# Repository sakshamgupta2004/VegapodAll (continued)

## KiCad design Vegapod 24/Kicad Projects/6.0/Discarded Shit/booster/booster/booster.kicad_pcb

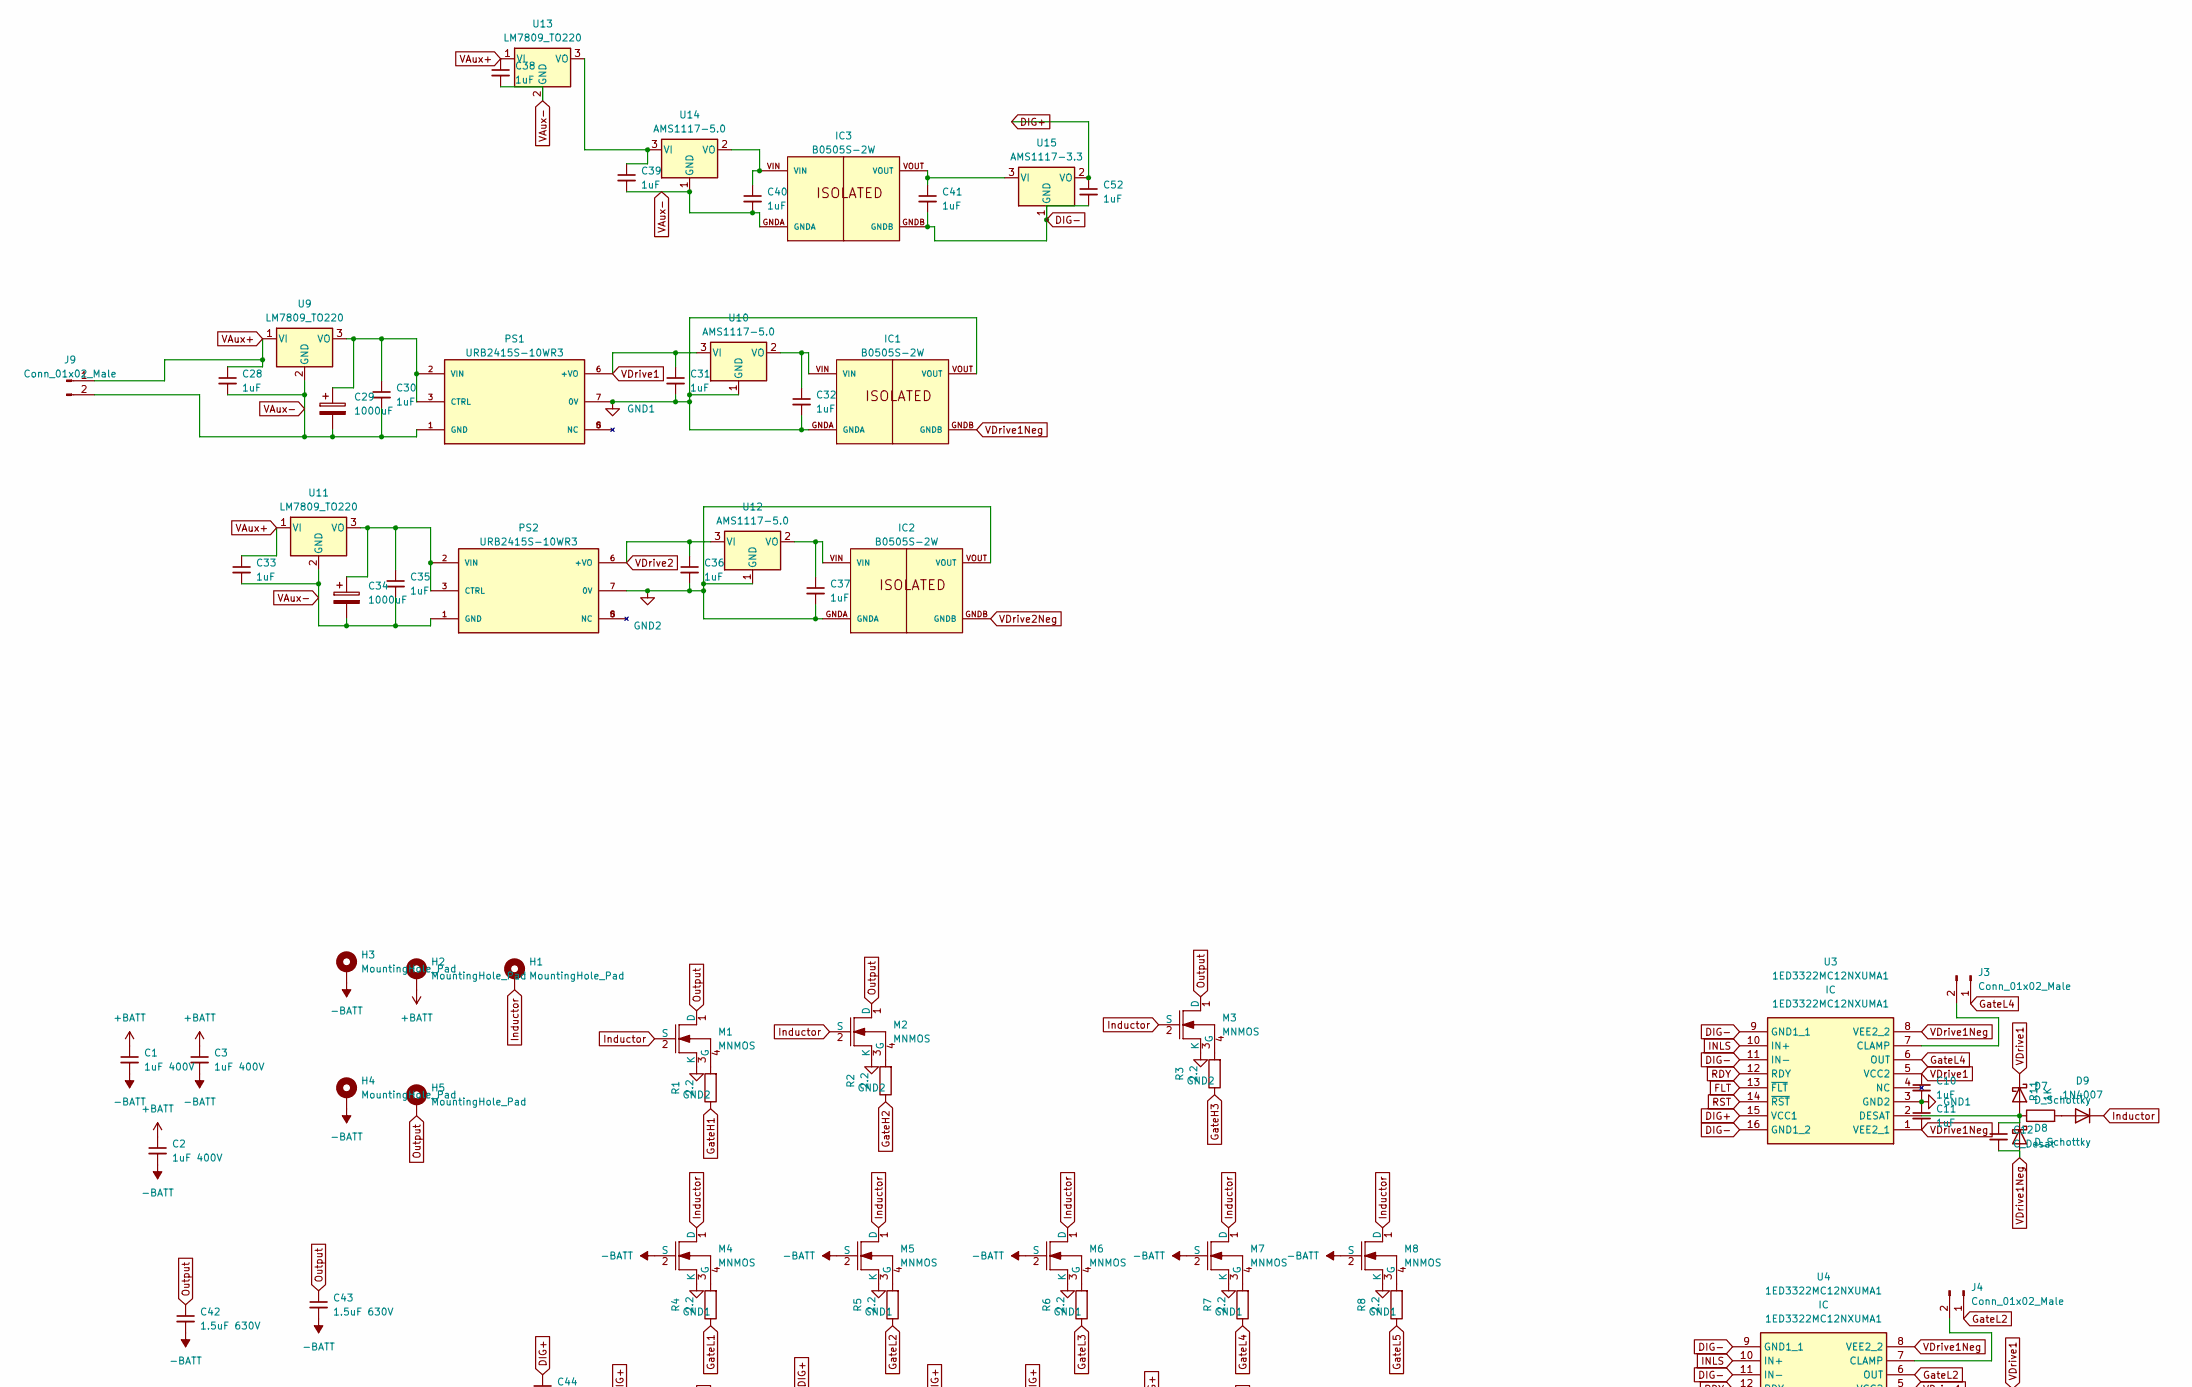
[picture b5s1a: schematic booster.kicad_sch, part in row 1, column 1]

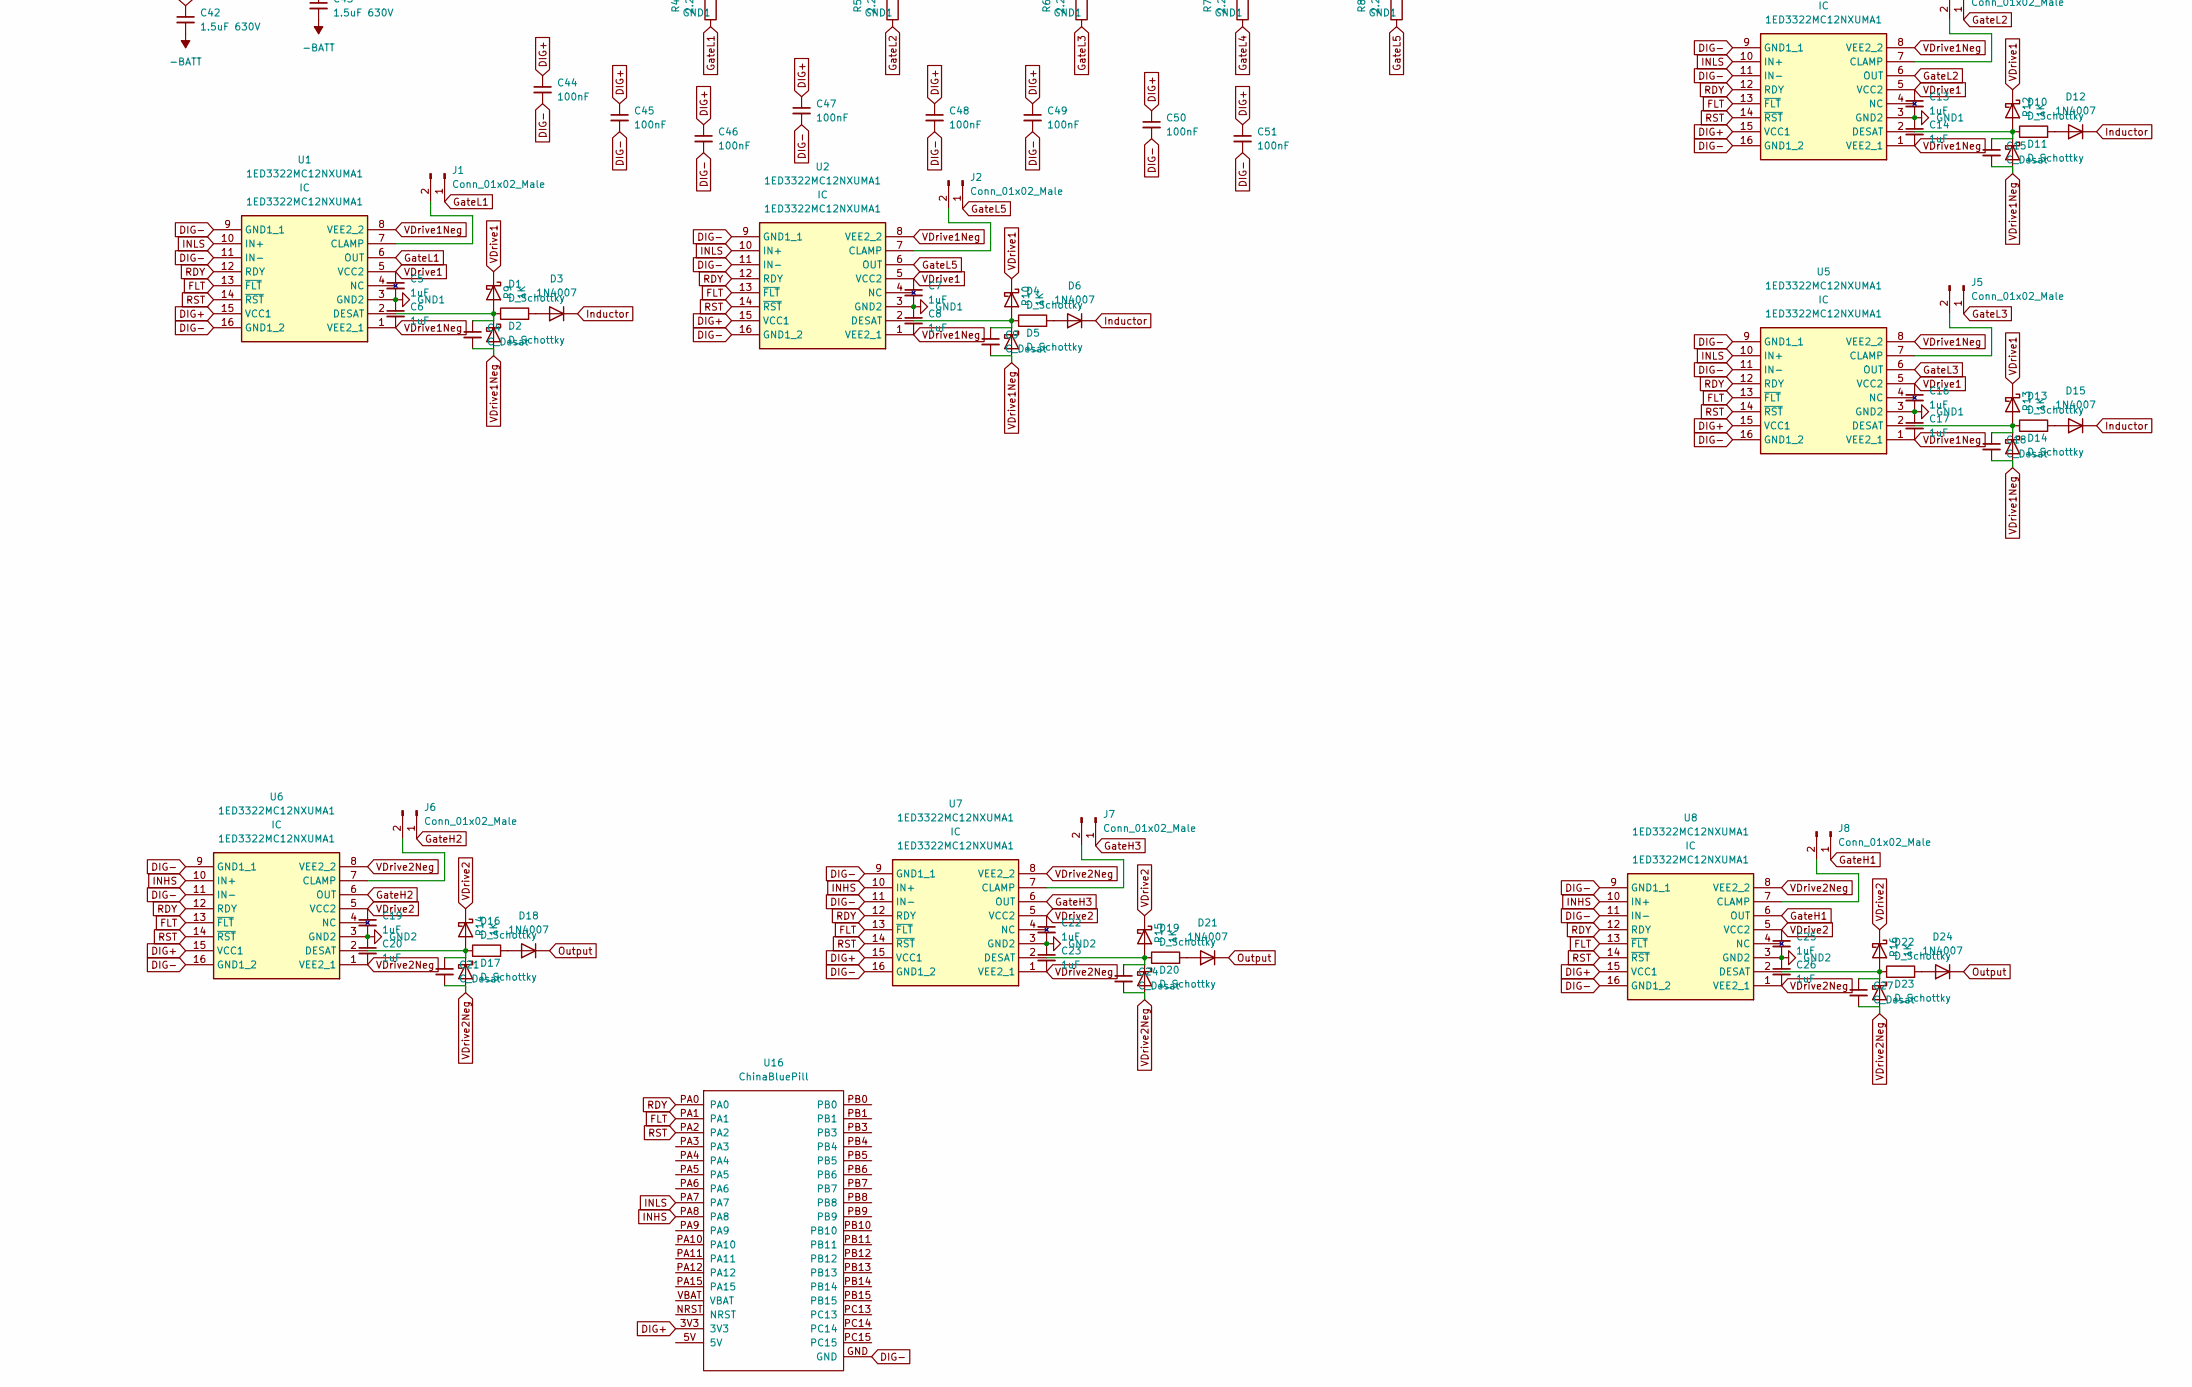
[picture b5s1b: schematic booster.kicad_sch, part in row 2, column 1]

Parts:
C1, C2, C3: 1uF 400V; C_Rect_L24.0mm_W8.3mm_P22.50mm_MKT
C4, C9, C12, C15, C18, C21, C24, C27: C_Desat; C_0603_1608Metric_Pad1.08x0.95mm_HandSolder
C5, C6, C7, C8, C10, C11, C13, C14, C16, C17, C19, C20, C22, C23, C25, C26, C28, C30, C31, C32, C33, C35, C36, C37, C38, C39, C40, C41, C52: 1uF; C_1206_3216Metric_Pad1.33x1.80mm_HandSolder
C29, C34: 1000uF; CAP_EEEFK1E102AQ
C42, C43: 1.5uF 630V; C_Rect_L29.0mm_W16.0mm_P27.50mm_MKT
C44, C45, C46, C47, C48, C49, C50, C51: 100nF; C_0603_1608Metric_Pad1.08x0.95mm_HandSolder
D1, D2, D4, D5, D7, D8, D10, D11, D13, D14, D16, D17, D19, D20, D22, D23: D_Schottky; D_SMA_Handsoldering
D3, D6, D9, D12, D15, D18, D21, D24: 1N4007; D_SMA_Handsoldering
H1, H2, H3, H4, H5: MountingHole_Pad; MountingHole_6.4mm_M6_Pad
IC1, IC2, IC3: B0505S-2W; MPN B0505S-2W; DigiKey_Part_Number 2725-B0505S-2W-ND
J1, J2, J3, J4, J5, J6, J7, J8: Conn_01x02_Male; PinHeader_1x02_P1.27mm_Vertical
J9: Conn_01x02_Male; JST_XH_S2B-XH-A_1x02_P2.50mm_Horizontal
M1, M2, M3, M4, M5, M6, M7, M8: MNMOS; TO-247-4_Horizontal_TabDown
PS1, PS2: URB2415S-10WR3; CONV_URB2415S-10WR3; PARTREV 2020.11.09-A/4; DigiKey_Part_Number 2725-URB2415S-10WR3-ND
R1, R2, R3, R4, R5, R6, R7, R8: 2.2; R_1206_3216Metric
R9, R10, R11, R12, R13, R14, R15, R16: 1K; R_0603_1608Metric_Pad0.98x0.95mm_HandSolder
U1, U2, U3, U4, U5, U6, U7, U8: 1ED3322MC12NXUMA1; SOIC127P1030X265-16N; Mouser Part Number 726-1ED3322MC12NXUMA
U9, U11, U13: LM7809_TO220; TO-220-3_Vertical
U10, U12, U14: AMS1117-5.0; SOT-223-3_TabPin2
U15: AMS1117-3.3; SOT-223-3_TabPin2
U16: ChinaBluePill

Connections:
+BATT: C1.1, C2.1, C3.1, H2.1
-BATT: C1.2, C2.2, C3.2, C42.2, C43.2, H3.1, H4.1, M4.2 (S), M5.2 (S), M6.2 (S), M7.2 (S), M8.2 (S)
DIG+: C44.1, C45.1, C46.1, C47.1, C48.1, C49.1, C50.1, C51.1, C52.1, U1.15 (VCC1), U2.15 (VCC1), U3.15 (VCC1), U4.15 (VCC1), U5.15 (VCC1), U6.15 (VCC1), U7.15 (VCC1), U8.15 (VCC1), U15.2 (VO), U16.3V3
DIG-: C41.2, C44.2, C45.2, C46.2, C47.2, C48.2, C49.2, C50.2, C51.2, C52.2, IC3.GNDB, U1.9 (GND1_1), U1.11 (IN-), U1.16 (GND1_2), U2.9 (GND1_1), U2.11 (IN-), U2.16 (GND1_2), U3.9 (GND1_1), U3.11 (IN-), U3.16 (GND1_2), U4.9 (GND1_1), U4.11 (IN-), U4.16 (GND1_2), U5.9 (GND1_1), U5.11 (IN-), U5.16 (GND1_2), U6.9 (GND1_1), U6.11 (IN-), U6.16 (GND1_2), U7.9 (GND1_1), U7.11 (IN-), U7.16 (GND1_2), U8.9 (GND1_1), U8.11 (IN-), U8.16 (GND1_2), U15.1 (GND), U16.GND
FLT: U1.13 (~FLT), U2.13 (~FLT), U3.13 (~FLT), U4.13 (~FLT), U5.13 (~FLT), U6.13 (~FLT), U7.13 (~FLT), U8.13 (~FLT), U16.PA1
GND1: C5.2, C6.1, C7.2, C8.1, C10.2, C11.1, C13.2, C14.1, C16.2, C17.1, C31.2, C32.2, IC1.GNDA, IC1.VOUT, M4.3 (K), M5.3 (K), M6.3 (K), M7.3 (K), M8.3 (K), PS1.7 (0V), U1.3 (GND2), U2.3 (GND2), U3.3 (GND2), U4.3 (GND2), U5.3 (GND2), U10.1 (GND)
GND2: C19.2, C20.1, C22.2, C23.1, C25.2, C26.1, C36.2, C37.2, IC2.GNDA, IC2.VOUT, M1.3 (K), M2.3 (K), M3.3 (K), PS2.7 (0V), U6.3 (GND2), U7.3 (GND2), U8.3 (GND2), U12.1 (GND)
GateH1: J8.1, R1.1, U8.6 (OUT)
GateH2: J6.1, R2.1, U6.6 (OUT)
GateH3: J7.1, R3.1, U7.6 (OUT)
GateL1: J1.1, R4.1, U1.6 (OUT)
GateL2: J4.1, R5.1, U4.6 (OUT)
GateL3: J5.1, R6.1, U5.6 (OUT)
GateL4: J3.1, R7.1, U3.6 (OUT)
GateL5: J2.1, R8.1, U2.6 (OUT)
INHS: U6.10 (IN+), U7.10 (IN+), U8.10 (IN+), U16.PA8
INLS: U1.10 (IN+), U2.10 (IN+), U3.10 (IN+), U4.10 (IN+), U5.10 (IN+), U16.PA7
Inductor: D3.1 (K), D6.1 (K), D9.1 (K), D12.1 (K), D15.1 (K), H1.1, M1.2 (S), M2.2 (S), M3.2 (S), M4.1 (D), M5.1 (D), M6.1 (D), M7.1 (D), M8.1 (D)
unnamed: C4.1, D1.2 (A), D2.1 (K), R9.1, U1.2 (DESAT)
unnamed: C9.1, D4.2 (A), D5.1 (K), R10.1, U2.2 (DESAT)
unnamed: C12.1, D7.2 (A), D8.1 (K), R11.1, U3.2 (DESAT)
unnamed: C15.1, D10.2 (A), D11.1 (K), R12.1, U4.2 (DESAT)
unnamed: C18.1, D13.2 (A), D14.1 (K), R13.1, U5.2 (DESAT)
unnamed: C21.1, D16.2 (A), D17.1 (K), R14.1, U6.2 (DESAT)
unnamed: C24.1, D19.2 (A), D20.1 (K), R15.1, U7.2 (DESAT)
unnamed: C27.1, D22.2 (A), D23.1 (K), R16.1, U8.2 (DESAT)
unnamed: C29.1, C30.1, PS1.2 (VIN), PS1.3 (CTRL), U9.3 (VO)
unnamed: C32.1, IC1.VIN, U10.2 (VO)
unnamed: C34.1, C35.1, PS2.2 (VIN), PS2.3 (CTRL), U11.3 (VO)
unnamed: C37.1, IC2.VIN, U12.2 (VO)
unnamed: C39.1, U13.3 (VO), U14.3 (VI)
unnamed: C40.1, IC3.VIN, U14.2 (VO)
unnamed: C41.1, IC3.VOUT, U15.3 (VI)
unnamed: D3.2 (A), R9.2
unnamed: D6.2 (A), R10.2
unnamed: D9.2 (A), R11.2
unnamed: D12.2 (A), R12.2
unnamed: D15.2 (A), R13.2
unnamed: D18.2 (A), R14.2
unnamed: D21.2 (A), R15.2
unnamed: D24.2 (A), R16.2
unnamed: J1.2, U1.7 (CLAMP)
unnamed: J2.2, U2.7 (CLAMP)
unnamed: J3.2, U3.7 (CLAMP)
unnamed: J4.2, U4.7 (CLAMP)
unnamed: J5.2, U5.7 (CLAMP)
unnamed: J6.2, U6.7 (CLAMP)
unnamed: J7.2, U7.7 (CLAMP)
unnamed: J8.2, U8.7 (CLAMP)
unnamed: M1.4 (G), R1.2
unnamed: M2.4 (G), R2.2
unnamed: M3.4 (G), R3.2
unnamed: M4.4 (G), R4.2
unnamed: M5.4 (G), R5.2
unnamed: M6.4 (G), R6.2
unnamed: M7.4 (G), R7.2
unnamed: M8.4 (G), R8.2
Output: C42.1, C43.1, D18.1 (K), D21.1 (K), D24.1 (K), H5.1, M1.1 (D), M2.1 (D), M3.1 (D)
RDY: U1.12 (RDY), U2.12 (RDY), U3.12 (RDY), U4.12 (RDY), U5.12 (RDY), U6.12 (RDY), U7.12 (RDY), U8.12 (RDY), U16.PA0
RST: U1.14 (~RST), U2.14 (~RST), U3.14 (~RST), U4.14 (~RST), U5.14 (~RST), U6.14 (~RST), U7.14 (~RST), U8.14 (~RST), U16.PA2
VAux+: C28.1, C33.1, C38.1, J9.1, U9.1 (VI), U11.1 (VI), U13.1 (VI)
VAux-: C28.2, C29.2, C30.2, C33.2, C34.2, C35.2, C38.2, C39.2, C40.2, IC3.GNDA, J9.2, PS1.1 (GND), PS2.1 (GND), U9.2 (GND), U11.2 (GND), U13.2 (GND), U14.1 (GND)
VDrive1: C5.1, C7.1, C10.1, C13.1, C16.1, C31.1, D1.1 (K), D4.1 (K), D7.1 (K), D10.1 (K), D13.1 (K), PS1.6 (+VO), U1.5 (VCC2), U2.5 (VCC2), U3.5 (VCC2), U4.5 (VCC2), U5.5 (VCC2), U10.3 (VI)
VDrive1Neg: C4.2, C6.2, C8.2, C9.2, C11.2, C12.2, C14.2, C15.2, C17.2, C18.2, D2.2 (A), D5.2 (A), D8.2 (A), D11.2 (A), D14.2 (A), IC1.GNDB, U1.1 (VEE2_1), U1.8 (VEE2_2), U2.1 (VEE2_1), U2.8 (VEE2_2), U3.1 (VEE2_1), U3.8 (VEE2_2), U4.1 (VEE2_1), U4.8 (VEE2_2), U5.1 (VEE2_1), U5.8 (VEE2_2)
VDrive2: C19.1, C22.1, C25.1, C36.1, D16.1 (K), D19.1 (K), D22.1 (K), PS2.6 (+VO), U6.5 (VCC2), U7.5 (VCC2), U8.5 (VCC2), U12.3 (VI)
VDrive2Neg: C20.2, C21.2, C23.2, C24.2, C26.2, C27.2, D17.2 (A), D20.2 (A), D23.2 (A), IC2.GNDB, U6.1 (VEE2_1), U6.8 (VEE2_2), U7.1 (VEE2_1), U7.8 (VEE2_2), U8.1 (VEE2_1), U8.8 (VEE2_2)

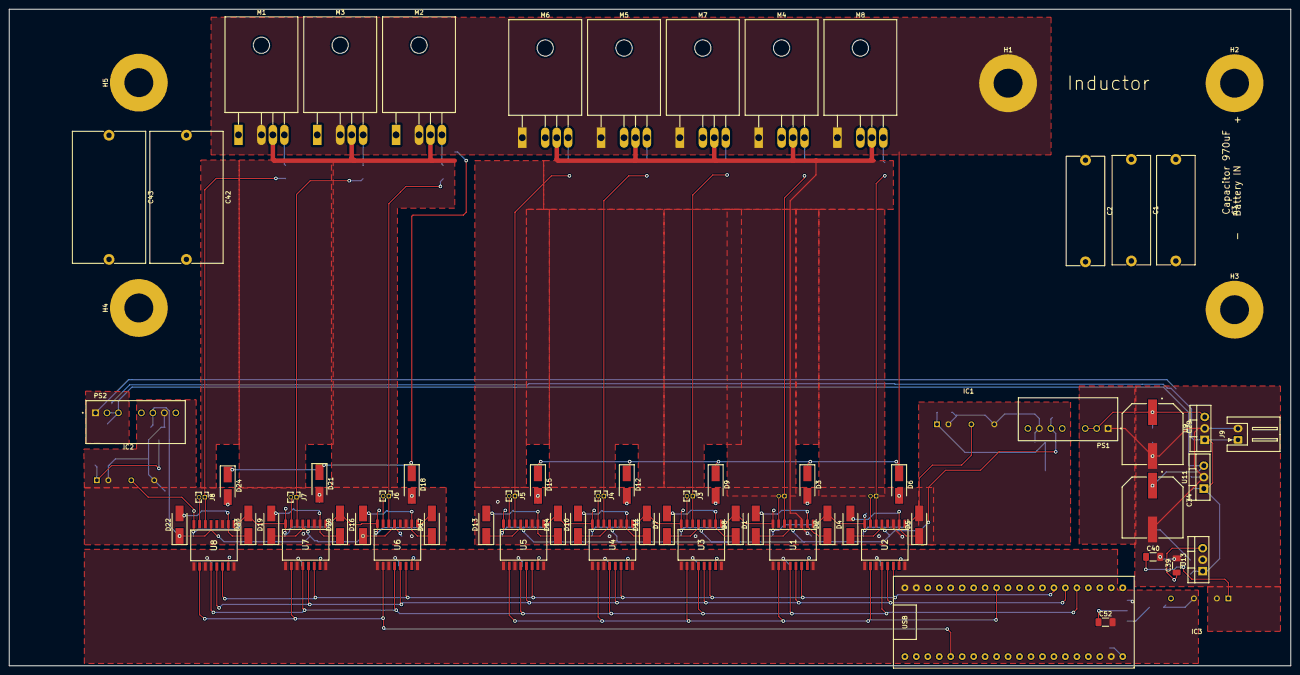
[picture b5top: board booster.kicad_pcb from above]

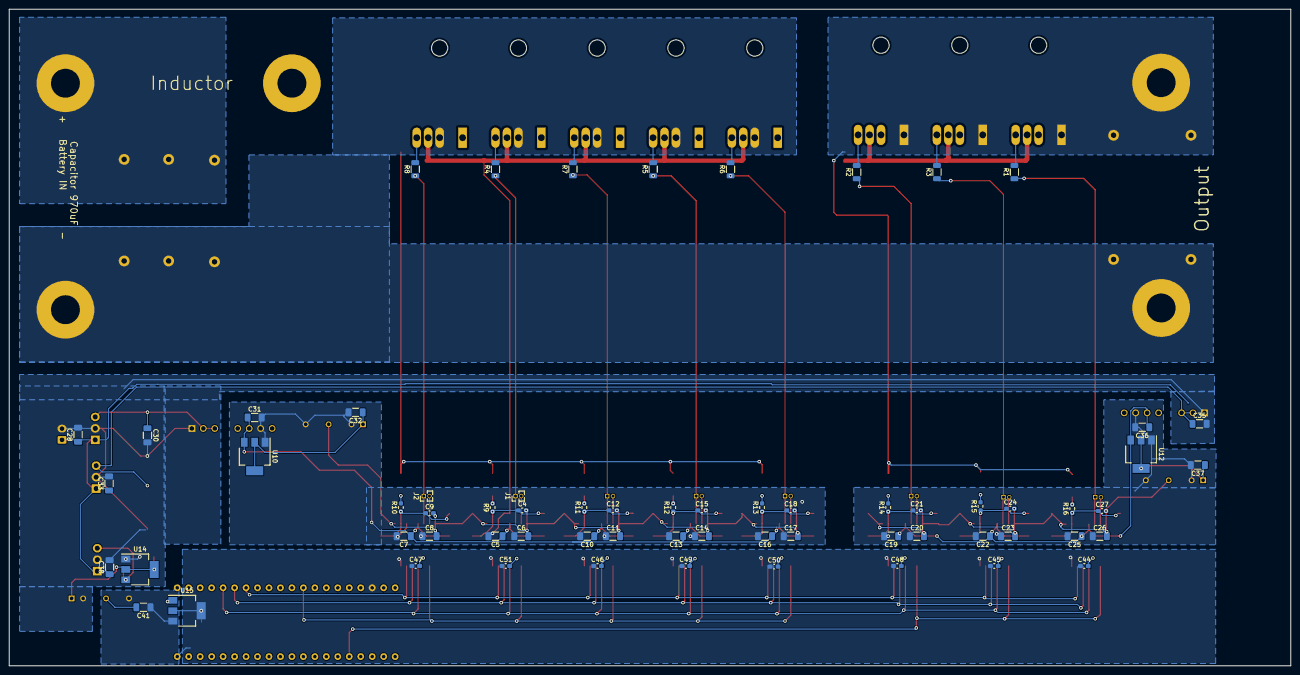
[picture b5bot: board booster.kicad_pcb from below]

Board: 2 copper layers, 283.8 x 145.4 mm, 135 parts (64 on the bottom side), 66 nets.

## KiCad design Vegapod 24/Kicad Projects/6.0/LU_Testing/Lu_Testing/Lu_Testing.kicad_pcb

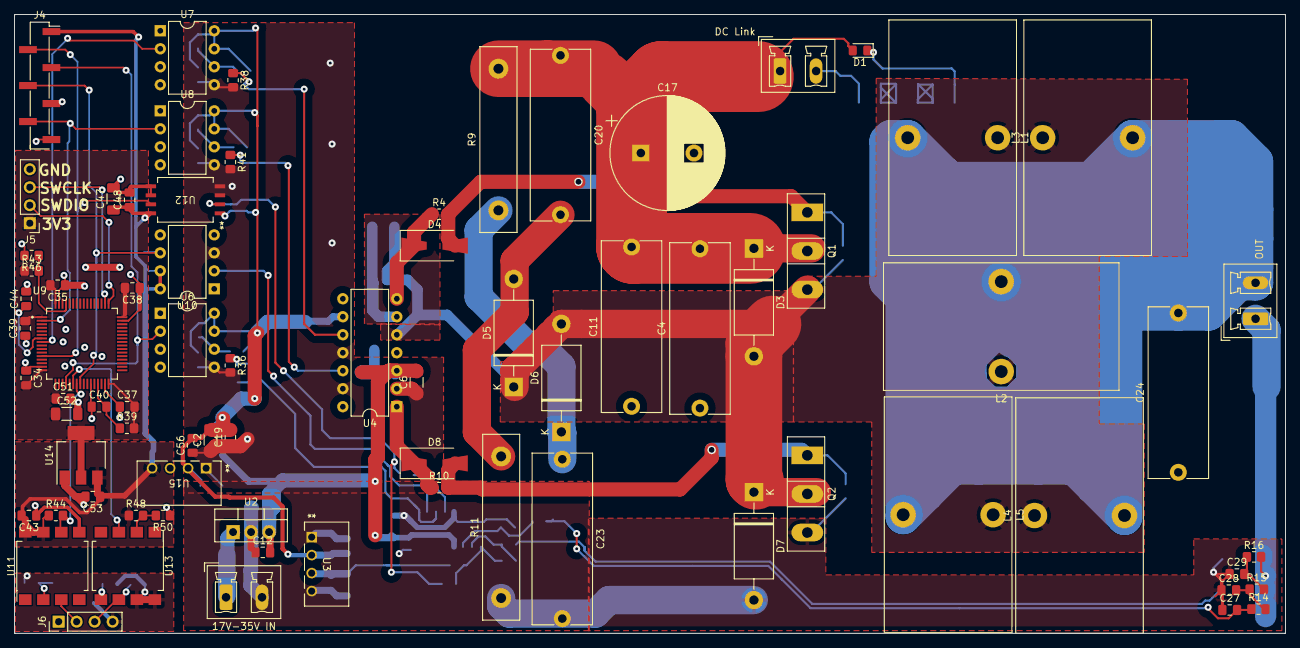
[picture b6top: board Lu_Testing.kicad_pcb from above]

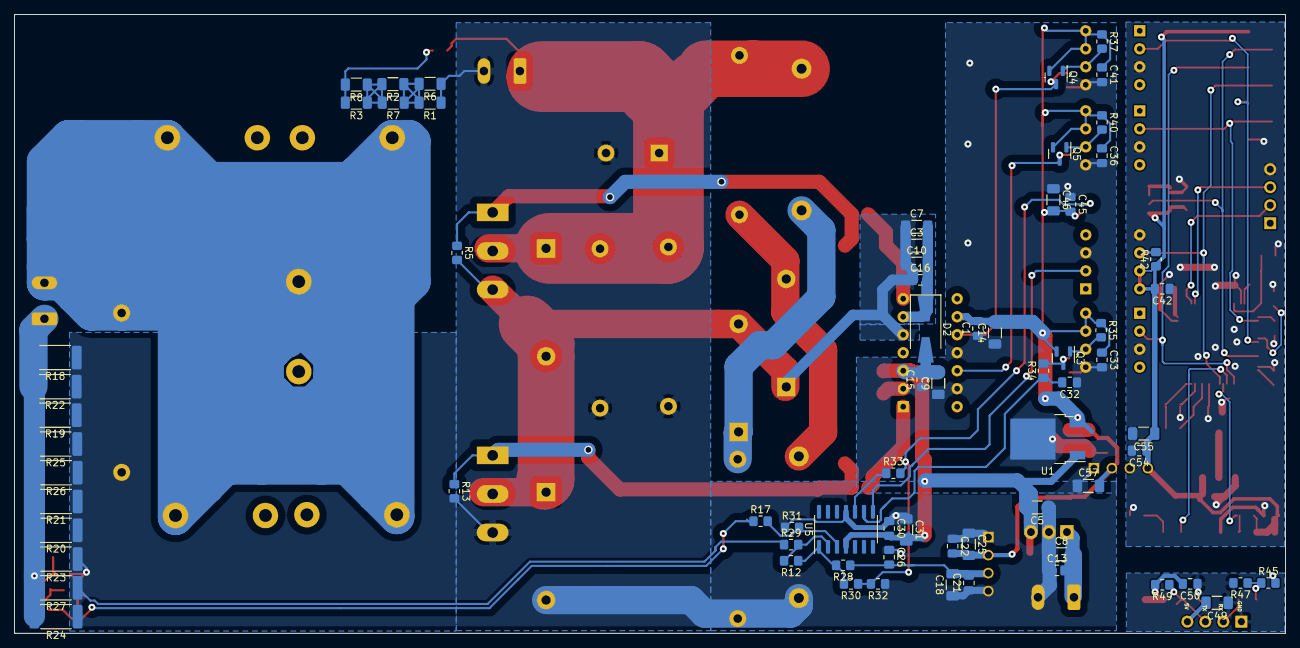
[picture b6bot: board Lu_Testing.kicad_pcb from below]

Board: 2 copper layers, 179.5 x 87.4 mm, 146 parts (70 on the bottom side), 56 nets.

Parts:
C1, C12, C13, C15, C16, C19, C21, C22, C26, C30, C33, C34, C35, C36, C37, C38, C39, C40, C41, C42, C43, C44, C45, C48, C50, C51, C53, C54, C56: 100n; C_0805_2012Metric_Pad1.18x1.45mm_HandSolder
C2, C3, C5, C6, C7, C8, C9, C10, C14, C18, C25, C31, C46, C47, C49, C52, C55, C57: 10u; C_1206_3216Metric_Pad1.33x1.80mm_HandSolder
C4, C11, C24: 1uF 400V; C_Rect_L24.0mm_W8.3mm_P22.50mm_MKT
C17: 56uF; CP_Radial_D16.0mm_P7.50mm
C20, C23: C_Snub; C_Rect_L24.0mm_W8.3mm_P22.50mm_MKT
C27, C28, C29, C32: 47n; C_0805_2012Metric_Pad1.18x1.45mm_HandSolder
D1: LED; D_0805_2012Metric_Pad1.15x1.40mm_HandSolder
D2, D4, D8: US1M; D_SMA-SMB_Universal_Handsoldering
D3, D5, D6, D7: MUR460; D_DO-201AE_P15.24mm_Horizontal
J1: DC Link; PhoenixContact_MCV_1,5_2-G-5.08_1x02_P5.08mm_Vertical
J2: 17V-35V IN; PhoenixContact_MCV_1,5_2-G-5.08_1x02_P5.08mm_Vertical
J3: OUT; PhoenixContact_MCV_1,5_2-G-5.08_1x02_P5.08mm_Vertical
J4: Conn_01x07_Male; PinHeader_1x07_P2.54mm_Vertical_SMD_Pin1Right
J5, J6: Conn_01x04_Male; PinHeader_1x04_P2.54mm_Vertical
L1, L2, L3, L4, L5: 330uH 5.2A; L_Toroid_Vertical_L33.0mm_W17.8mm_P12.70mm_Pulse_KM-5
Q1, Q2: Q_NMOS_GDS; TO-247-3_Vertical
Q3, Q4, Q5: Q_PMOS_GSD; SOT-23
R1, R2, R3, R6, R7, R8: 22K; R_1206_3216Metric_Pad1.30x1.75mm_HandSolder
R4, R10, R39: 10; R_0805_2012Metric_Pad1.20x1.40mm_HandSolder
R5, R13: 1K; R_0805_2012Metric_Pad1.20x1.40mm_HandSolder
R9, R11: R_Snub; R_Box_L26.0mm_W5.0mm_P20.00mm
R12, R17, R29, R31, R33: 10k; R_0805_2012Metric_Pad1.20x1.40mm_HandSolder
R14, R15, R16, R34: 220; R_0805_2012Metric_Pad1.20x1.40mm_HandSolder
R18, R19, R20, R21, R22, R23, R24, R25, R26, R27: 0.1Ohm 3W; R_2512_6332Metric_Pad1.40x3.35mm_HandSolder
R28, R32, R35, R36, R37, R38, R40, R41, R42, R44, R45, R47, R48, R49, R50: 470; R_0805_2012Metric_Pad1.20x1.40mm_HandSolder
R30: 1k; R_0805_2012Metric_Pad1.20x1.40mm_HandSolder
R43: Open Circuit; R_0805_2012Metric_Pad1.20x1.40mm_HandSolder
R46: Short out; R_0805_2012Metric_Pad1.20x1.40mm_HandSolder
U1: KA78M05_TO252; TO-252-2
U2: LM7815_TO220; TO-220-3_Vertical
U3, U15: B0505S-1WR3; B0505S_MNS
U4: IR2110; DIP-14_W7.62mm
U5: LM324; SOIC-14_3.9x8.7mm_P1.27mm
U6, U7, U8, U10: 6N137; DIP-8_W7.62mm
U9: STM32G474RET6; QFP50P1200X1200X160-64N
U11, U13: 6N137; SSO-8_6.7x9.8mm_P2.54mm_Clearance8mm
U12: ADUM4195-1BRIZ; RI-8-1_ADI
U14: AMS1117-3.3; SOT-223-3_TabPin2

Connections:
5VCOMM: C49.2, C50.2, J6.4, R45.2, R49.2, U13.7 (EN), U13.8 (VCC)
+3.3V: C34.2, C35.2, C37.2, C38.2, C39.2, C51.1, C52.1, J5.1, R39.2, R43.1, U9.1 (VBAT), U9.16 (VDD), U9.32 (VDD), U9.48 (VDD), U9.64 (VDD), U14.2 (VO)
+5V: C1.2, C2.2, C14.2, C19.2, C22.2, C25.2, C33.1, C36.1, C41.1, C45.2, C46.2, C56.2, C57.2, Q3.2 (S), Q4.2 (S), Q5.2 (S), R35.1, R37.1, R40.1, U1.3 (VO), U3.2 (VIN), U4.9 (VDD), U6.7 (EN), U6.8 (VCC), U7.7 (EN), U7.8 (VCC), U8.7 (EN), U8.8 (VCC), U12.1 (VDD2), U15.2 (VIN)
+5VD: C42.2, C43.2, C47.1, C48.1, C53.1, C54.1, C55.1, J4.1, R42.1, R44.1, R48.1, U10.7 (EN), U10.8 (VCC), U11.7 (EN), U11.8 (VCC), U12.8 (VDD1), U14.3 (VI), U15.4 (+VO)
+15V: C5.2, C6.2, C9.2, C12.2, C15.2, C30.2, C31.2, D2.2 (A), U1.1 (VI), U2.3 (VO), U4.3 (VCC), U5.4 (V+)
-5V: C18.2, C21.2, C26.2, R28.1, U3.3 (0V)
A0: R30.1, R32.2, R33.2, U12.2 (VIN)
CO: U5.8, U10.2 (A)
DA0: J4.2, U9.12 (PA0), U12.7 (VOUT)
DC Link+: C4.2, C11.2, C17.1, C20.1, D1.2 (A), D3.1 (K), J1.1, Q1.2 (D), R9.2
DC Link-: C1.1, C2.1, C4.1, C5.1, C6.1, C8.1, C9.1, C11.1, C12.1, C13.1, C14.1, C15.1, C17.2, C18.1, C19.1, C21.1, C22.1, C23.2, C24.1, C25.1, C26.1, C27.1, C28.1, C29.1, C30.1, C31.1, C32.1, C33.2, C36.2, C41.2, C45.1, C46.1, C56.1, C57.1, D7.2 (A), J1.2, J2.2, Q2.3 (S), R1.1, R6.1, R11.1, R13.2, R18.1, R19.1, R20.1, R21.1, R22.1, R23.1, R24.1, R25.1, R26.1, R27.1, R29.1, R31.1, R32.1, R36.2, R38.2, R41.2, U1.2 (GND), U2.2 (GND), U3.1 (GND), U3.4 (+VO), U4.2 (COM), U4.11 (SD), U4.13 (VSS), U5.11 (V-), U6.5 (GND), U7.5 (GND), U8.5 (GND), U10.3 (C), U12.3 (SHTD), U12.4 (GND2), U15.1 (GND)
DFB: J4.4, R42.2, U9.24 (PB0), U10.6 (VO)
DHIN: J4.5, U7.2 (A), U9.8 (PC0)
DLIN: J4.6, U8.2 (A), U9.2 (PC13)
DPWMADJ: J4.3, U6.2 (A), U9.20 (PA6)
GNDCOMM: C49.1, C50.1, J6.1, R47.2, U13.5 (GND)
GNDD: C34.1, C35.1, C37.1, C38.1, C39.1, C40.1, C42.1, C43.1, C44.2, C47.2, C48.2, C51.2, C52.2, C53.2, C54.2, C55.2, J4.7, J5.4, R46.2, R50.1, U6.3 (C), U7.3 (C), U8.3 (C), U9.15 (VSS), U9.27 (VSSA), U9.31 (VSS), U9.47 (VSS), U9.63 (VSS), U10.5 (GND), U11.5 (GND), U12.5 (GND1), U12.6 (NC), U14.1 (GND), U15.3 (0V)
HIN: Q4.3 (D), R38.1, U4.10 (HIN)
LIN: Q5.3 (D), R41.1, U4.12 (LIN)
unnamed: C3.2, C7.2, C10.2, C16.2, D2.1 (K), U4.6 (VB)
unnamed: C8.2, C13.2, J2.1, U2.1 (VI)
unnamed: C20.2, D5.2 (A), R11.2
unnamed: C23.1, D6.1 (K), R9.1
unnamed: C24.2, J3.2, L1.2, L2.2, L3.2, L4.2, L5.2
unnamed: C27.2, R14.1, R17.1
unnamed: C28.2, R14.2, R15.1
unnamed: C29.2, R15.2, R16.1
unnamed: C32.2, R34.1, U5.9 (-)
unnamed: C40.2, R39.1, U9.29 (VDDA)
unnamed: C44.1, U9.7 (PG10-~RST)
unnamed: D1.1 (K), R3.2, R8.2
unnamed: D4.1 (K), R4.1, U4.7 (HO)
unnamed: D4.2 (A), Q1.1 (G), R4.2, R5.1
unnamed: D8.1 (K), R10.1, U4.1 (LO)
unnamed: D8.2 (A), Q2.1 (G), R10.2, R13.1
unnamed: J3.1, R16.2, R18.2, R19.2, R20.2, R21.2, R22.2, R23.2, R24.2, R25.2, R26.2, R27.2
unnamed: Q3.1 (G), R35.2, U6.6 (VO)
unnamed: Q3.3 (D), R34.2, R36.1
unnamed: Q4.1 (G), R37.2, U7.6 (VO)
unnamed: Q5.1 (G), R40.2, U8.6 (VO)
unnamed: R1.2, R2.1, R6.2, R7.1
unnamed: R2.2, R3.1, R7.2, R8.1
unnamed: R12.1, R28.2, R30.2, U5.1
unnamed: R12.2, R29.2, U5.2 (-)
unnamed: R17.2, R31.2, U5.3 (+)
unnamed: R33.1, U5.10 (+)
unnamed: R43.2, R46.1, U9.61 (PB8-BOOT0)
unnamed: R45.1, R47.1, U11.2 (A)
unnamed: R48.2, R50.2, U13.2 (A)
RXCOMM: J6.2, U11.3 (C)
RXD: R44.2, U9.23 (PC5), U11.6 (VO)
SWCLK: J5.3, U9.50 (PA14)
SWDIO: J5.2, U9.49 (PA13)
TXCOMM: J6.3, R49.1, U13.6 (VO)
TXD: U9.22 (PC4), U13.3 (C)
VS: C3.1, C7.1, C10.1, C16.1, D3.2 (A), D5.1 (K), D6.2 (A), D7.1 (K), L1.1, L2.1, L3.1, L4.1, L5.1, Q1.3 (S), Q2.2 (D), R5.2, U4.5 (VS)

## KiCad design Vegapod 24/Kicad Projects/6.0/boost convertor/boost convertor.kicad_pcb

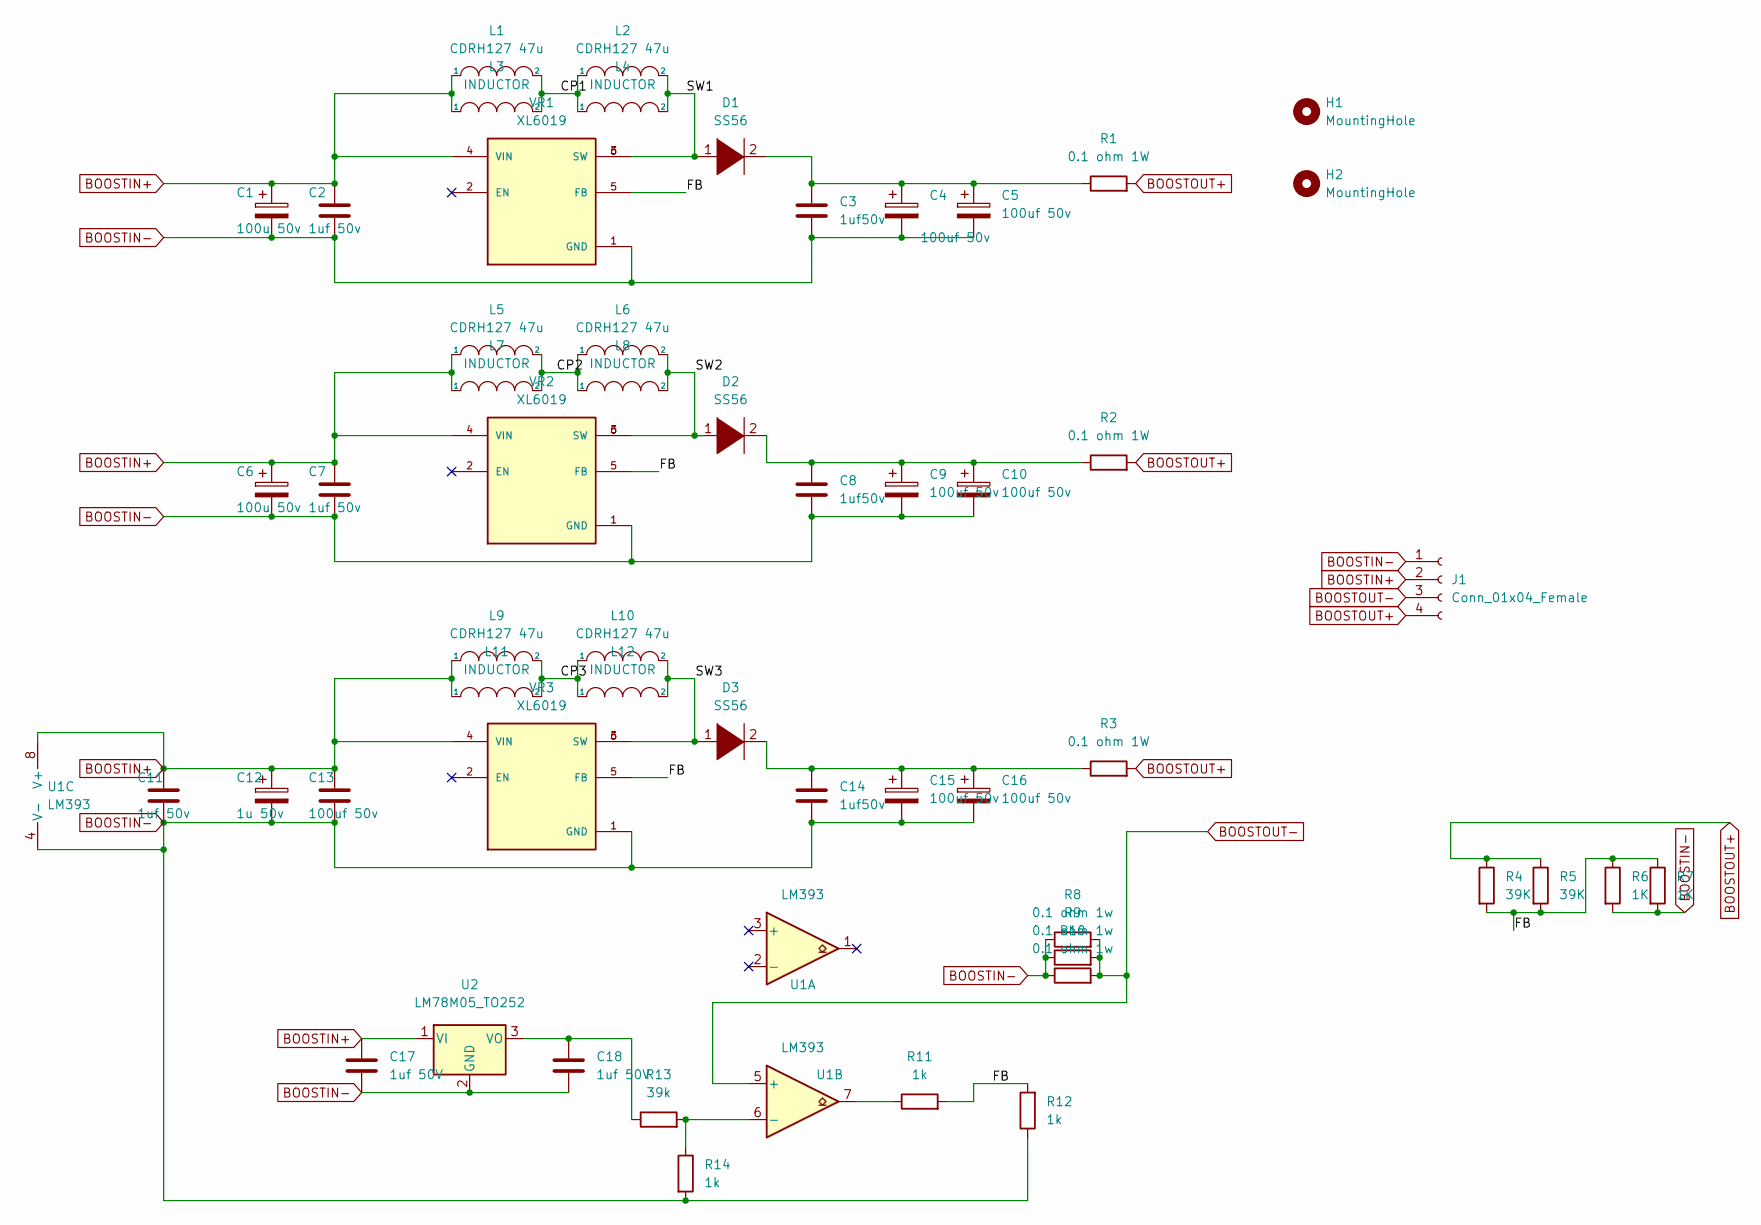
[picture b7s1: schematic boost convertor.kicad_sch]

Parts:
C1, C6: 100u 50v; CP_Elec_10x10.5
C2, C7, C11: 1uf 50v; C_1206_3216Metric
C3, C8, C14: 1uf50v; C_1206_3216Metric
C4, C5, C9, C10, C13, C15, C16: 100uf 50v; CP_Elec_10x10.5
C12: 1u 50v; C_1206_3216Metric
C17, C18: 1uf 50V; C_1206_3216Metric
D1, D2, D3: SS56; D_SMA-SMB_Universal_Handsoldering
H1, H2: MountingHole; MountingHole_3.2mm_M3
J1: Conn_01x04_Female; PhoenixContact_MSTBVA_2,5_4-G-5,08_1x04_P5.08mm_Vertical
L1, L2, L5, L6, L9, L10: CDRH127 47u; L_12x12mm_H8mm
L3, L4, L7, L8, L11, L12: INDUCTOR; L_12x12mm_H8mm
R1, R2, R3: 0.1 ohm 1W; R_2512_6332Metric
R4, R5: 39K; R_0805_2012Metric
R6, R7: 1K; R_0805_2012Metric
R8, R9, R10: 0.1 ohm 1w; R_2512_6332Metric
R11, R12, R14: 1k; R_0805_2012Metric
R13: 39k; R_0805_2012Metric
U1: LM393; SO-8_5.3x6.2mm_P1.27mm
U2: LM78M05_TO252; TO-252-2
VR1, VR2, VR3: XL6019; TO-263-5_TabPin6; PARTREV 1.1

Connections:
/CP1: L1.2, L2.1, L3.2, L4.1
/CP2: L5.2, L6.1, L7.2, L8.1
/CP3: L9.2, L10.1, L11.2, L12.1
/FB: R4.2, R5.2, R6.1, R7.1, R11.2, R12.2, VR1.5 (FB), VR2.5 (FB), VR3.5 (FB)
/SW1: D1.1 (K), L2.2, L4.2, VR1.3 (SW), VR1.6 (SW)
/SW2: D2.1 (K), L6.2, L8.2, VR2.3 (SW), VR2.6 (SW)
/SW3: D3.1 (K), L10.2, L12.2, VR3.3 (SW), VR3.6 (SW)
BOOSTIN+: C1.1, C2.1, C6.1, C7.1, C11.1, C12.1, C13.1, C17.1, J1.2, L1.1, L3.1, L5.1, L7.1, L9.1, L11.1, U1.8 (V+), U2.1 (VI), VR1.4 (VIN), VR2.4 (VIN), VR3.4 (VIN)
BOOSTIN-: C1.2, C2.2, C3.2, C4.2, C5.2, C6.2, C7.2, C8.2, C9.2, C10.2, C11.2, C12.2, C13.2, C14.2, C15.2, C16.2, C17.2, C18.2, J1.1, R6.2, R7.2, R8.1, R9.1, R10.1, R12.1, R14.2, U1.4 (V-), U2.2 (GND), VR1.1 (GND), VR2.1 (GND), VR3.1 (GND)
BOOSTOUT+: J1.4, R1.2, R2.2, R3.2, R4.1, R5.1
BOOSTOUT-: J1.3, R8.2, R9.2, R10.2, U1.5 (+)
unnamed: C3.1, C4.1, C5.1, D1.2 (A), R1.1
unnamed: C8.1, C9.1, C10.1, D2.2 (A), R2.1
unnamed: C14.1, C15.1, C16.1, D3.2 (A), R3.1
unnamed: C18.1, R13.1, U2.3 (VO)
unnamed: R11.1, U1.7
unnamed: R13.2, R14.1, U1.6 (-)
